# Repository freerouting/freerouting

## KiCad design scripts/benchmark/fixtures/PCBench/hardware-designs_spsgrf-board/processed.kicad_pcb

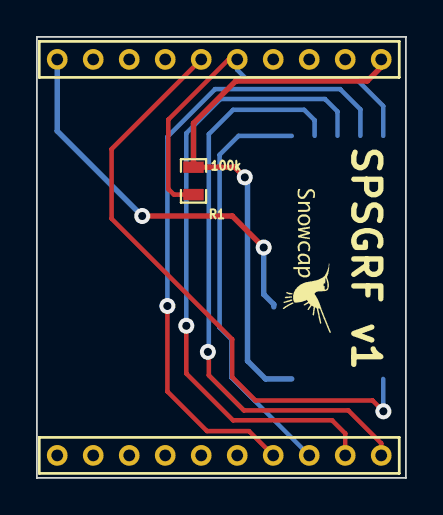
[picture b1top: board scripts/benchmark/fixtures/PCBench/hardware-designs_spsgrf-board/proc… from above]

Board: 2 copper layers, 20.5 x 24.5 mm, 4 parts (1 on the bottom side), 8 nets.

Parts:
CN1: RB-CN10; RB_CN10_2mm
Noname_1: LOGO_SNOWCAP_FRONT_SMALL
R1: 100k; SM0603_Resistor
U1: SPSGRF

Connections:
GND: CN1.10, U1.6
unnamed: CN1.6, U1.1
unnamed: CN1.5, R1.2, U1.11
unnamed: CN1.11, U1.8
unnamed: CN1.12, U1.9
unnamed: CN1.14, U1.10
unnamed: CN1.13, U1.7
VCC: CN1.1, R1.1, U1.5

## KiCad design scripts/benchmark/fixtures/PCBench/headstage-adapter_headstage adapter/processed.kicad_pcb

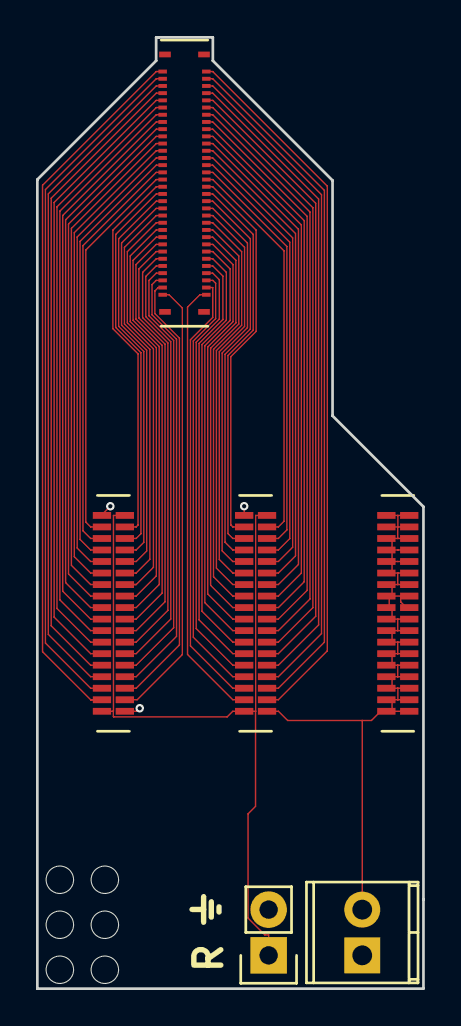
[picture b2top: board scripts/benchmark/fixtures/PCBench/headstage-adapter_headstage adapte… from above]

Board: 4 copper layers, 21.4 x 52.8 mm, 12 parts (0 on the bottom side), 66 nets.

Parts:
JP1: Jumper_NO_Small; Socket_Strip_Straight_1x02
M1, M2, M3, M4, M5, M6: #0 drill hole; #0_drill_hole
P1: 502426-6410; Molex_SlimStack_receptacle_64_0.4mm_pitch
P2: 1725656; TerminalBlock_Pheonix_MPT-2.54mm_2pol
U1, U2, U3: A79026-001; omnetics_connector_36_pin

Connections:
/1: P1.63, U1.3
/2: P1.1, U1.4
/3: P1.61, U1.5
/4: P1.3, U1.6
/5: P1.59, U1.7
/6: P1.5, U1.8
/7: P1.57, U1.9
/8: P1.7, U1.10
/9: P1.55, U1.11
/10: P1.9, U1.12
/11: P1.53, U1.13
/12: P1.11, U1.14
/13: P1.51, U1.15
/14: P1.13, U1.16
/15: P1.49, U1.17
/16: P1.15, U1.18
/17: P1.47, U1.19
/18: P1.17, U1.20
/19: P1.45, U1.21
/20: P1.19, U1.22
/21: P1.43, U1.23
/22: P1.21, U1.24
/23: P1.41, U1.25
/24: P1.23, U1.26
/25: P1.39, U1.27
/26: P1.25, U1.28
/27: P1.37, U1.29
/28: P1.27, U1.30
/29: P1.35, U1.31
/30: P1.29, U1.32
/31: P1.33, U1.33
/32: P1.31, U1.34
/33: P1.2, U2.3
/34: P1.64, U2.4
/35: P1.4, U2.5
/36: P1.62, U2.6
/37: P1.6, U2.7
/38: P1.60, U2.8
/39: P1.8, U2.9
/40: P1.58, U2.10
/41: P1.10, U2.11
/42: P1.56, U2.12
/43: P1.12, U2.13
/44: P1.54, U2.14
/45: P1.14, U2.15
/46: P1.52, U2.16
/47: P1.16, U2.17
/48: P1.50, U2.18
/49: P1.18, U2.19
/50: P1.48, U2.20
/51: P1.20, U2.21
/52: P1.46, U2.22
/53: P1.22, U2.23
/54: P1.44, U2.24
/55: P1.24, U2.25
/56: P1.42, U2.26
/57: P1.26, U2.27
/58: P1.40, U2.28
/59: P1.28, U2.29
/60: P1.38, U2.30
/61: P1.30, U2.31
/62: P1.36, U2.32
/63: P1.32, U2.33
/64: P1.34, U2.34
/G: JP1.2, P2.2, U1.1, U1.36, U2.1, U2.36, U3.1, U3.2, U3.3, U3.4, U3.5, U3.6, U3.7, U3.8, U3.9, U3.10, U3.11, U3.12, U3.13, U3.14, U3.15, U3.16, U3.17, U3.18, U3.19, U3.20, U3.21, U3.22, U3.23, U3.24, U3.25, U3.26, U3.27, U3.28, U3.29, U3.30, U3.31, U3.32, U3.33, U3.34, U3.35, U3.36
/R: JP1.1, P2.1, U1.2, U1.35, U2.2, U2.35

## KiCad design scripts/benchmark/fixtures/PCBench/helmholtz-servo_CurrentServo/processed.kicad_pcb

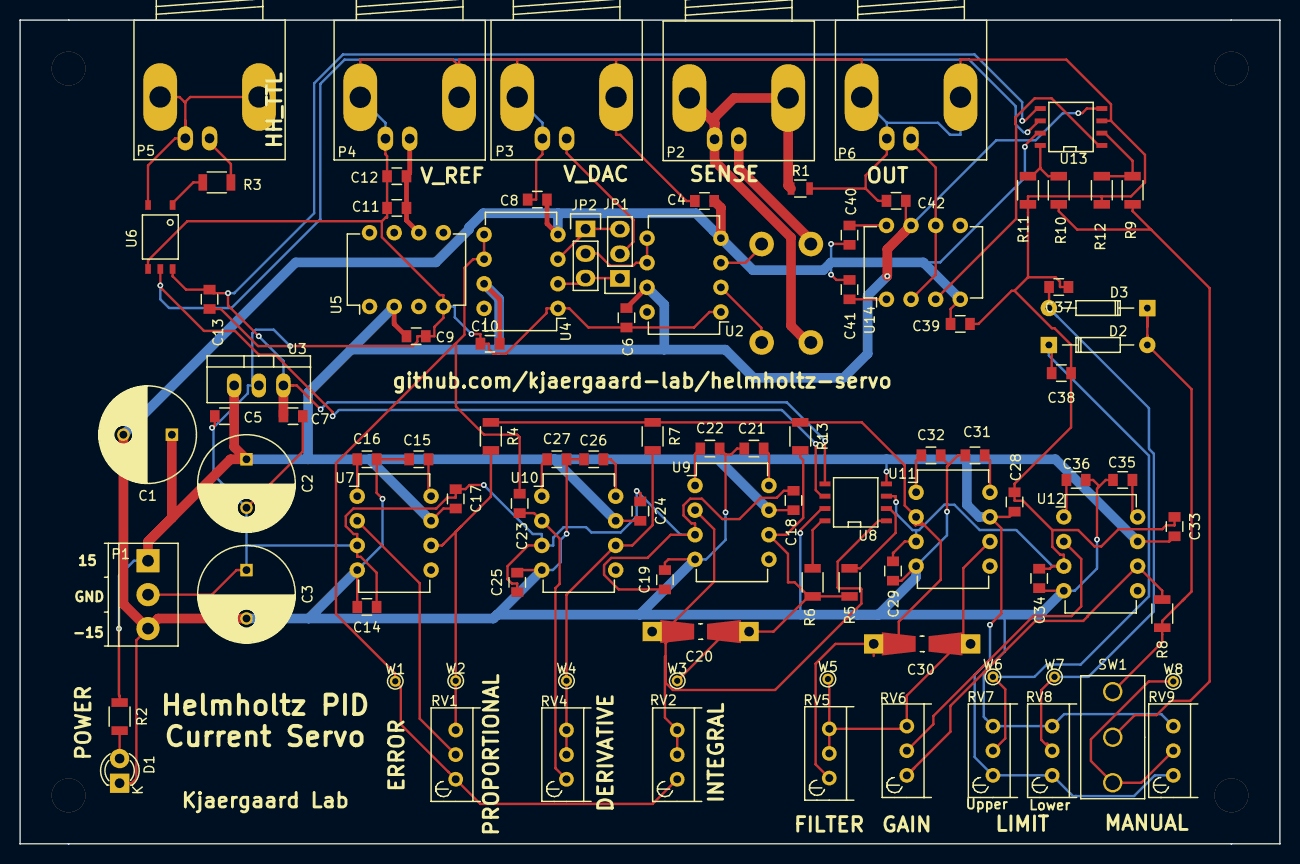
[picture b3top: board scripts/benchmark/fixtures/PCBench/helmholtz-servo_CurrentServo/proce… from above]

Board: 2 copper layers, 130.0 x 85.0 mm, 97 parts (1 on the bottom side), 52 nets.

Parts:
C1: 22u; C_Radial_D10_L13_P5
C2, C3: 100u; C_Radial_D10_L16_P5
C4, C6, C8, C10, C12, C13, C14, C15, C16, C17, C18, C19, C21, C22, C23, C24, C25, C26, C27, C28, C29, C31, C32, C33, C34, C35, C36, C37, C38, C39, C40, C41, C42: 100n; C_0805
C5: 330n; C_0805
C7: 10n; C_0805
C9, C11: 2.2u; C_0805
C20, C30: 100n; Resistor_SMD+THTuniversal_0805to1206_RM10_HandSoldering
D1: LED; LED-3MM
D2, D3: D; Diode_DO-35_SOD27_Horizontal_RM10
JP1, JP2: JUMPER3; Pin_Header_Straight_1x03
P1: POWER; TerminalBlock_Pheonix_PT-3.5mm_3pol
P2: SENSE; BNC_Socket_TYCO-AMP_LargePads
P3: V_DAC; BNC_Socket_TYCO-AMP_LargePads
P4: VREF; BNC_Socket_TYCO-AMP_LargePads
P5: HH_IN; BNC_Socket_TYCO-AMP_LargePads
P6: OUT; BNC_Socket_TYCO-AMP_LargePads
R1: 0R; R_0805
R2: 1K2; R_1206
R3: 330; R_1206
R4, R7, R13: 10K; R_1206
R5, R10, R12: DNP; R_1206
R6: 3K3; R_1206
R8: 51K; R_1206
R9, R11: 50; R_1206
RV1, RV2, RV4, RV5, RV9: 10K; Potentiometer_Bourns_3296W_3-8Zoll_Inline_ScrewUp
RV6: 100K; Potentiometer_Bourns_3296W_3-8Zoll_Inline_ScrewUp
RV7, RV8: 2K; Potentiometer_Bourns_3296W_3-8Zoll_Inline_ScrewUp
SW1: 1AS2T2B4M2RE; Switch_SPDT_4.7mm
U1: VHP4Z
U2, U4: INA105; DIP-8_W7.62mm
U3: 78L05; TO-220_Neutral123_Vertical
U5: MAX6350; DIP-8_W7.62mm
U6: TLP116A
U7, U9, U10, U11, U12, U14: TC7650; DIP-8_W7.62mm
U8, U13: DG419; SOIC-8-N
W1: ERROR; PINTST
W2: PROP; PINTST
W3: INT; PINTST
W4: DERIV; PINTST
W5: FILTER; PINTST
W6: ULIM; PINTST
W7: LLIM; PINTST
W8: MANUAL; PINTST

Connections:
/OutputConditioning/CTRL_IN: C30.2, R4.1, R7.1, R13.1, RV5.1, U11.2
/OutputConditioning/LLIMIT: C37.2, D3.2, RV8.2, W7.1
/OutputConditioning/SIG_OUT: P6.1, U14.2, U14.6
/OutputConditioning/ULIMIT: C38.2, D2.1, RV7.2, W6.1
/PIDAmps/ERROR: C23.2, RV1.1, RV2.1, U4.5, U4.6, W1.1
GND: C2.2, C3.1, C4.2, C5.2, C6.1, C7.2, C8.1, C9.2, C10.1, C11.2, C12.2, C13.2, C14.1, C17.1, C18.1, C19.1, C24.1, C25.1, C28.1, C29.1, C33.1, C34.1, C37.1, C38.1, C39.2, C42.1, P1.2, P3.2, P4.2, P6.2, R1.2, R11.2, R12.2, U2.1, U3.2, U4.1, U5.4, U6.4, U7.3, U8.3, U9.3, U10.3, U11.3, U12.3, U13.3
HH_TTL: U6.5, U8.6, U13.6
unnamed: C11.1, C12.1, P4.1, U5.6
unnamed: C15.1, U7.8
unnamed: C16.1, U7.1
unnamed: C20.1, R5.1, R6.1, R13.2, U9.6, W3.1
unnamed: C20.2, RV2.2, RV2.3, U8.1, U9.2
unnamed: C21.1, U9.8
unnamed: C22.1, U9.1
unnamed: C23.1, RV4.1, U10.2
unnamed: C26.1, U10.8
unnamed: C27.1, U10.1
unnamed: C30.1, RV5.2, RV5.3, RV6.3, U11.6, W5.1
unnamed: C31.1, U11.8
unnamed: C32.1, U11.1
unnamed: C35.1, U12.8
unnamed: C36.1, U12.1
unnamed: C40.1, U14.8
unnamed: C41.1, U14.1
unnamed: D1.2, R2.2
unnamed: D2.2, D3.1, R8.1, SW1.1
unnamed: JP1.1, JP2.3, U4.2
unnamed: JP1.2, P3.1
unnamed: JP1.3, JP2.1, U4.3
unnamed: JP2.2, U2.5, U2.6
unnamed: P2.1, U1.1
unnamed: P2.2, R1.1, U1.2
unnamed: P5.1, R3.2
unnamed: P5.2, U6.3
unnamed: R3.1, U6.1
unnamed: R4.2, RV1.3, U7.6, W2.1
unnamed: R5.2, U8.2
unnamed: R6.2, U8.8
unnamed: R7.2, RV4.2, RV4.3, U10.6, W4.1
unnamed: R8.2, RV6.1, U12.6
unnamed: R10.1, R11.1, U13.8
unnamed: R9.2, R10.2, SW1.2
unnamed: R9.1, R12.1, U13.2
unnamed: RV1.2, U7.2
unnamed: RV6.2, U12.2
unnamed: RV9.2, SW1.3, W8.1
unnamed: U1.3, U2.3
unnamed: U1.4, U2.2
unnamed: U13.1, U14.3
VCC: C7.1, C13.1, U3.3, U6.6, U8.5, U13.5
VDD: C1.1, C2.1, C5.1, C6.2, C9.1, C10.2, C17.2, C18.2, C24.2, C28.2, C33.2, C42.2, P1.1, R2.1, RV7.1, RV8.1, RV9.1, U2.7, U3.1, U4.7, U5.2, U7.7, U8.4, U9.7, U10.7, U11.7, U12.7, U13.4, U14.7
VSS: C1.2, C3.2, C4.1, C8.2, C14.2, C15.2, C16.2, C19.2, C21.2, C22.2, C25.2, C26.2, C27.2, C29.2, C31.2, C32.2, C34.2, C35.2, C36.2, C39.1, C40.2, C41.2, D1.1, P1.3, RV7.3, RV8.3, RV9.3, U2.4, U4.4, U7.4, U8.7, U9.4, U10.4, U11.4, U12.4, U13.7, U14.4
